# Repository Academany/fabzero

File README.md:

# `fabzero` Digital Fabrication Program (formerly Pre Academy)

This repository hosts the `fabzero` official program. It was originally designed to fill knowledge gaps and aimed to prepare students to succeed and improve their experience during [Fab Academy](http://fabacademy.org). Over the years, it has been growing into a multidisciplinary program, where a customized learning path is designed and crafted to the specific needs of the group.

## What's new

* Adding more design thinking and design principles
* Increasing documentation tools and repository management
* Increasing lessons in CAD (2D, 3D, parametric, advanced and simulation)
* Based in commonly used [FOSS](https://en.wikipedia.org/wiki/Free_and_open-source_software)
* Removing some topics that are common with Fab Academy
* `new` Topics related to fab lab management
* `new` Topics to encourage gender equality and respectful workplace

## Let's get started!

[:point_right: Click here to go to `fabzero` official curriculum](program/summary.md)

[:point_right: Click here to browse the participants archive of past experiences](program/cycles.md)

## Questions and comments

This repository is maintained and updated by Francisco Sanchez and Sibu Saman. If you have questions or inquiries about the course content please do not hesitate to raise an issue or contact me francisco [at] fabfoundation [dot] org. Happy to help!

This repository keeps a mirror copy both in GitHub and GitLab

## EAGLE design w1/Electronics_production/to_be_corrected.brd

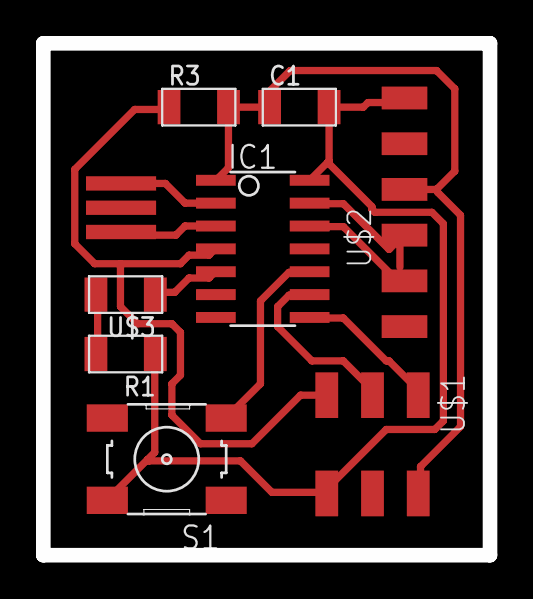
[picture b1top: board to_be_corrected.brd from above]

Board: 2 copper layers, 24.8 x 28.4 mm, 9 parts (0 on the bottom side), 13 nets.

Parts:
C1: 1uF; C1206FAB
IC1: ATTINY44-SSU; SOIC14
R1: 330; R1206FAB
R3: 10K; R1206FAB
S1: 6MM_SWITCH
U$1: AVRISPSMD; 2X03SMD
U$2: FTDI-SMD-HEADER; 1X06SMD
U$3: LEDFAB1206; LED1206FAB
U$4: RESONATOR; EFOBM

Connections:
GND: C1.2, IC1.14, R1.1, S1.2, U$1.6, U$2.1, U$4.2
unnamed: IC1.5, U$3.1
unnamed: IC1.13, U$2.4
unnamed: IC1.4, R3.1, U$1.5
unnamed: IC1.3, U$4.3
unnamed: IC1.2, U$4.1
unnamed: IC1.8, U$1.1
unnamed: IC1.7, U$1.4
unnamed: IC1.9, U$1.3
unnamed: R1.2, U$3.2
unnamed: IC1.10, S1.3
unnamed: IC1.12, U$2.5
VCC: C1.1, IC1.1, R3.2, U$1.2, U$2.3

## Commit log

2016-09-26 Introduced Pre Academy
2016-09-26 Further release notes
2016-09-29 outlining the daily topics
2016-11-07 recreating file structure
2016-11-07 adding nav links
2016-11-07 Fixed wrong link
2016-11-07 Adding first content to prefab SE
2016-11-07 added students gitlab repo
2016-11-07 swapped d2 and d3 in w1
2016-11-11 working on git chapter
2016-11-12 messing up everything again
2016-11-13 Learning the command line
2016-11-15 command line 101 changes
2016-11-17 More linux command line exercises
2016-11-26 outlining openscad and others
2016-11-26 just add FOSS
2016-11-26 final intro review
2016-11-30 adding academnay programs
2016-11-30 push at 562mph and 41000 ft
2016-11-30 minor aditions in an A380, -53C chilly outside
2016-12-02 adding 64 bit
2016-12-03 added archive web address
2016-12-03 changes to git repositories
2016-12-03 changed license to CC
2016-12-03 added md extension to license
2016-12-04 modified matrix gif
2016-12-06 Design principles
2016-12-06 Electronics prodution- board files
2016-12-06 improved doc page
2016-12-06 detailing and completing git section
2016-12-06 rewrite advices
2016-12-06 preparing audio and video documentation
2016-12-07 added simple script
2016-12-07 fixing some errors
2016-12-07 fixing doc formatting
2016-12-08 several updates from thrusday
2016-12-08 fixing doc page, take 3
2016-12-09 Assorted friday updates, code mainly
2016-12-13 code and simulation
2016-12-17 added assembly
2016-12-19 understanding permissions
2017-01-23 fixing incompletions
2017-02-08 updating w1
2017-02-11 fixed typo in graphicsmagick
2017-02-11 Preparing links for post install scripts
2017-05-19 Modified code
2017-05-27 Preparing for 2018 cycle
2017-10-23 sibu- test push, update names
2017-11-20 added links
2017-11-25 Add Jordan participants
2017-11-25 clarified syllabus
2017-11-25 renamed shopbotcnc.md
2017-11-25 added 2018 page
2017-11-26 fixing webpage link
2017-11-27 fixed intro links
2017-11-27 fixed and added links
2017-11-27 added multimedia to doc.md
2017-11-27 added requisites to pass pre academy
2017-11-27 more command line tools
2017-11-27 fixed tables
2017-12-04 added kokopelli tutorial
2017-12-04 electronics rearrangements
2017-12-04 merging with Dubai
2017-12-05 switching to fabcloud.org
2017-12-05 added sample code for production
2017-12-05 fixed sample code
2017-12-05 added books
2017-12-07 advanced programming
2017-12-10 fixed timer interrupt link
2017-12-10 merged timer interrupts with timers
2017-12-10 fixed timer images
2017-12-10 openscad rtfm fixed
2017-12-11 splitted timers
2017-12-13 added video!
2017-12-14 fixed ADC link
2017-12-19 added color harmony page
2018-10-28 Updated PreAcademy2018 status and added gitignore
2018-10-28 updated contact information
2018-11-15 rebranding to fab zero
2018-11-16 recreating the curriculum
2018-11-16 creating placeholder files
2018-11-16 get out of the comfort zone
2018-11-16 image alignment fix
2018-11-16 comfort image fix
2018-11-16 make your path
2018-11-16 sharing economy
2018-11-17 slap du
2018-11-17 fixed past edition links
2018-11-17 brain overflow
2018-11-18 why document
2018-11-18 idea behind microcontroller
2018-11-18 git topic cycle independent
2018-11-19 time management
2018-11-19 typos and grammar
2018-11-19 spiral and debug
2018-11-19 final project sillabus
2018-11-20 freecad sillabus
2018-11-20 shopbot sillabus
2018-11-22 videoconference with BlueJeans
2018-11-22 troubleshooting and maintenance sillabus
2018-11-23 removed advanced cad
2018-11-23 cleanup
2018-12-01 gender equality and respectful workplace
2018-12-01 splitted cycles
2018-12-01 rewrite intro
2018-12-04 learning by doing snippets
2018-12-06 modified gender equality sillabus
2018-12-11 final project
2018-12-12 grammar fix
2018-12-13 coding is powerful
2019-01-13 linting and TOC introduction
2019-01-13 updated summary and readme
2019-01-13 TOC for introduction
2019-01-13 updated TOC
2019-01-14 Linting and adding TOCs to electronics
2019-01-14 moved file size from command line to git
2019-01-14 linting interrupts
2019-01-14 time counter linting and TOC
2019-01-14 timer interrupts linting and TOC
2019-01-14 attempt to fix syntax highlighting
2019-01-14 test syntax highlight fix
2019-01-14 emoji support
2019-01-15 smoke test developed
2019-01-15 mark WIP pages
2019-01-15 mark WIP and added TOCs
2019-01-15 added back navigation links
2019-01-15 rearrange folders
2019-01-17 moved notebook to documentation
2019-01-17 added youtube-dl as documentation tool
2019-01-17 documenting the final project
2019-01-17 craft your work
2019-01-17 master the presentation
2019-01-17 refine final project
2019-01-18 the good, the bad and the ugly
2019-01-22 busy is the new stupid
2019-01-22 gitlab pm
2019-01-22 boards in gitlab
2019-01-22 project management exercises
2019-01-22 added goal of the unit
2019-01-22 git goal and remove non fundamental stuff
2019-01-22 commandline goal and removed non fundamental stuff
2019-01-24 refactoring
2019-01-25 branching
2019-01-26 removed kokopelli oldies
2019-02-21 sibu added TODO outline and some spell-check
2019-02-22 sibu: updated electronics101
2019-02-22 preparing to mirror
2019-02-22 check dual push
2019-03-05 sibu: timer
2019-03-19 pwm update
2019-03-19 test commit
2019-03-24 list participants
2019-03-24 list participants fix
2019-03-24 split list
2019-03-24 sibu: notes after review, fixed some of the links to participant pages
2019-03-26 sibu: sample codes
2019-03-28 sibu: sample codes errata
2019-03-29 refined participant list
2019-03-29 removed old feedback
2019-03-29 final projects selected
2019-03-29 second batch final projects
2019-03-30 sibu: added kicad library
2019-04-02 sibu: timer code errata
2019-04-02 sibu: tqfp32 modded for 0.4mm milling
2019-04-05 chintu to local team
2019-07-11 added egypt program
2019-07-11 moving folder
2019-07-11 rollback
2019-08-06 fab15 updates
2019-08-06 electroncis design md update
2019-08-07 prog resources update
2019-08-07 interrupt resource update
2019-08-07 added blink-problem
2019-08-07 double pcb edit
2019-08-07 sibu:iot
2019-08-08 sibu:iot reference update
2019-11-03 keeping forked repos up to date
2019-12-07 formatting cli
2019-12-07 fabzero women data
2020-01-01 it runs
2020-12-05 edit title
2022-01-28 notepad directory
2022-01-28 added 6th edition
2022-01-28 Update intro.md to 2022
2022-01-29 fix links
2022-01-29 add images
2022-01-29 fix image position
2022-01-31 Fixed some issues with git
2022-01-31 Update to 2022
2022-01-31 adding flameshot
2022-02-01 fixed ssh keypair link
2022-02-01 install intructions
2022-02-01 image title
2022-02-01 image raster vector
2022-02-01 revert to convert instead of montage
2022-02-01 Student List Bhutan
2022-02-01 Update bhutan-student-list.md manish
2022-02-01 add video tools
